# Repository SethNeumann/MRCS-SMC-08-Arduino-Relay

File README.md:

# REPO NAME: MRCS-SMC-08-Arduino-Relay 
## License: Creative Commons Attribution-NonCommercial-ShareAlike

8 channel tortoise driver after Chubb's SMC-12 with Arduino relay input

One of the common use cases for our Arduino Relay Controller is setting up a yard or staging ladder. An Arduino relay is often used
to control power on tracks by steering or simply turning power on or off. Another case is to use the SPDT contacts of a common "Arduino
Relay" to control MTB's MPx series switch machines. This board controls 8 Tortoise-by-Circuitron (TM) stall motors using the circuit 
described by Dr Bruce Chubb MMR in his CMRI Application Handbook V 3.0, pages 7-12 thru 7-17, available from JLC Enterprises 
[this is an excellent reference on Model Railroad control and signaling and should be in the library of EVERY model railroader interested 
in electronics]. 

The design of the SMC is modular where a single LM324 quad Op Amp/Comparator controls a pair of Tortii. I have implemented 8 circuits and provided an input
connector compatible with the most common 8 channel Arduino Relay. In this way your code on the Arduino Relay Controller doesn't need to know
whether the device is a Tortoise or an MPx, you simply use the appropriate board.

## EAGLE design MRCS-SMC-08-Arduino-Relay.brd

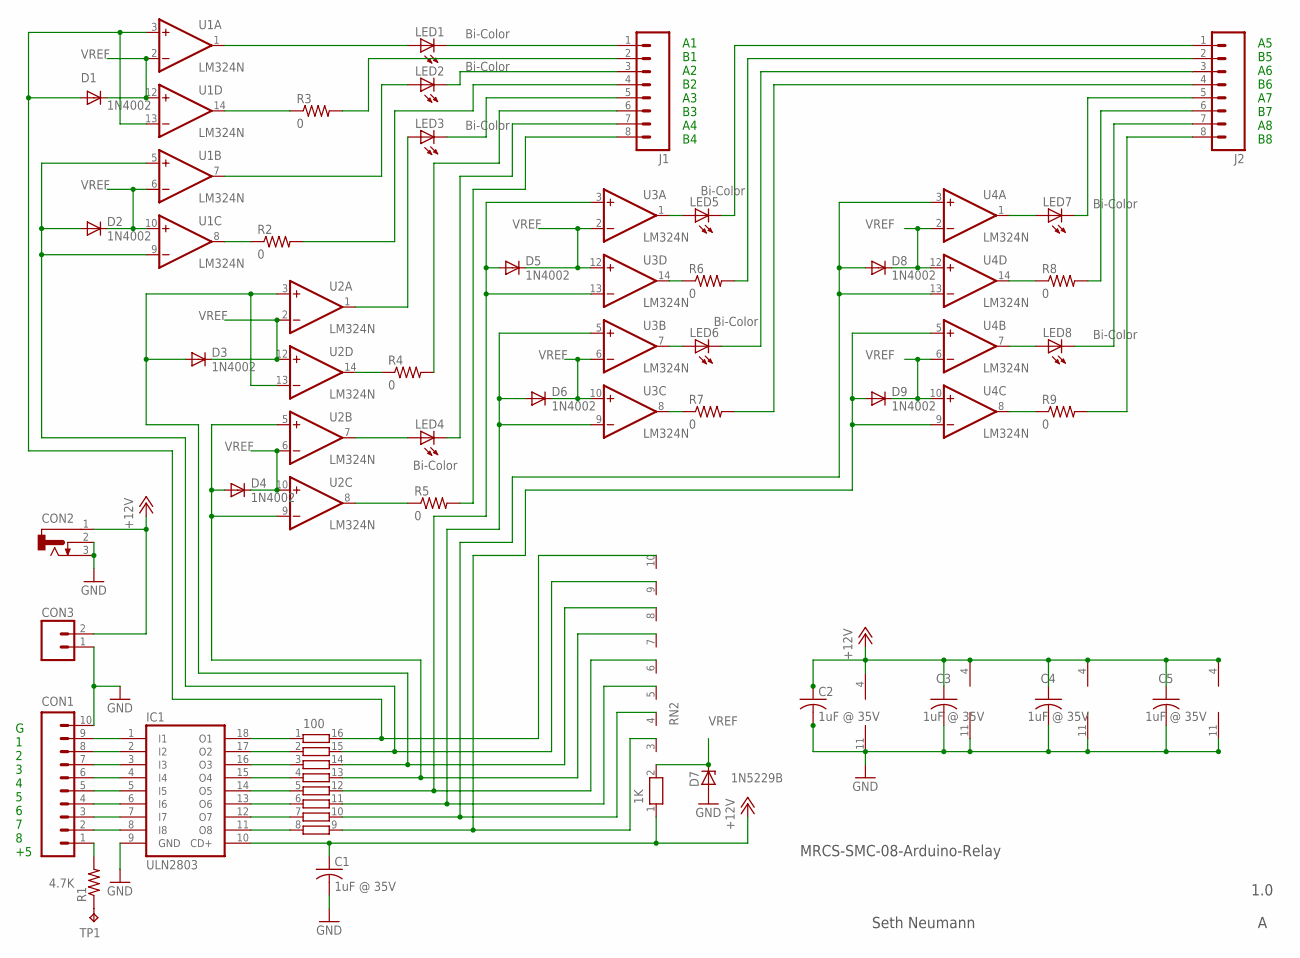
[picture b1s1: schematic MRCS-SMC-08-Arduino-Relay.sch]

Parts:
C1, C2, C3, C4, C5: 1uF @ 35V; C-PTH-0.100
CON1: CONNECTOR-M10LOCK; 1X10_LOCK
CON2: CONNECTOR-DC-POWER-S; DCJ0202-SMALL
CON3: CONNECTOR-M023.5MM-LOCK; SCREWTERMINAL-3.5MM-2_LOCK
D1, D2, D3, D4, D5, D6, D8, D9: 1N4002; DIODE-1N4001
D7: 1N5229B; ZDIO-5
IC1: ULN2803; DIL18
J1, J2: CONNECTOR-M08LOCK; 1X08_LOCK
LED1, LED2, LED3, LED4, LED5, LED6, LED7, LED8: Bi-Color; LED3MM
R1: 4.7K; AXIAL-0.4-RES
R2, R3, R4, R5, R6, R7, R8, R9: 0; CUT-R
RN1: 100; DIL16
RN2: 1K; RN-10
TP1: TPPAD1-13; P1-13
U1, U2, U3, U4: LM324N; DIL14

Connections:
+12V: C1.1, C2.1, C3.1, C4.1, C5.1, CON2.1, CON3.2 (B), IC1.10 (CD+), RN2.1, U1.4 (V+), U2.4 (V+), U3.4 (V+), U4.4 (V+)
GND: C1.2, C2.2, C3.2, C4.2, C5.2, CON1.10, CON2.2, CON2.3, CON3.1 (A), D7.A, IC1.9 (GND), U1.11 (V-), U2.11 (V-), U3.11 (V-), U4.11 (V-)
unnamed: R1.P$1 (1), TP1.TP
unnamed: CON1.9, IC1.1 (I1)
unnamed: CON1.8, IC1.2 (I2)
unnamed: CON1.7, IC1.3 (I3)
unnamed: CON1.6, IC1.4 (I4)
unnamed: CON1.5, IC1.5 (I5)
unnamed: CON1.4, IC1.6 (I6)
unnamed: CON1.3, IC1.7 (I7)
unnamed: CON1.2, IC1.8 (I8)
unnamed: D2.A, RN1.15 (2), RN2.9, U1.5 (+IN), U1.9 (-IN)
unnamed: R3.P2 (1), U1.14 (OUT)
unnamed: CON1.1, R1.P$2 (2)
unnamed: J1.7, LED4.K (C)
unnamed: J1.2, R3.P1 (2)
unnamed: LED1.A, U1.1 (OUT)
unnamed: J1.1, LED1.K (C)
unnamed: IC1.18 (O1), RN1.1
unnamed: IC1.17 (O2), RN1.2 (1)
unnamed: LED2.A, U1.7 (OUT)
unnamed: R2.P2 (1), U1.8 (OUT)
unnamed: J1.4, R2.P1 (2)
unnamed: J1.3, LED2.K (C)
unnamed: IC1.16 (O3), RN1.3 (1)
unnamed: IC1.15 (O4), RN1.4 (1)
unnamed: IC1.14 (O5), RN1.5 (1)
unnamed: IC1.13 (O6), RN1.6 (1)
unnamed: IC1.12 (O7), RN1.7 (1)
unnamed: IC1.11 (O8), RN1.8 (1)
unnamed: LED7.A, U4.1 (OUT)
unnamed: R8.P2 (1), U4.14 (OUT)
unnamed: D6.A, RN1.11 (2), RN2.5, U3.5 (+IN), U3.9 (-IN)
unnamed: LED5.A, U3.1 (OUT)
unnamed: LED4.A, U2.7 (OUT)
unnamed: LED3.A, U2.1 (OUT)
unnamed: D3.A, RN1.14 (2), RN2.8, U2.3 (+IN), U2.13 (-IN)
unnamed: J1.5, LED3.K (C)
unnamed: D1.A, RN1.16 (2), RN2.10, U1.3 (+IN), U1.13 (-IN)
unnamed: R4.P2 (1), U2.14 (OUT)
unnamed: J1.6, R4.P1 (2)
unnamed: D4.A, RN1.13 (2), RN2.7, U2.5 (+IN), U2.9 (-IN)
unnamed: R5.P2 (1), U2.8 (OUT)
unnamed: J1.8, R5.P1 (2)
unnamed: R6.P2 (1), U3.14 (OUT)
unnamed: D5.A, RN1.12 (2), RN2.6, U3.3 (+IN), U3.13 (-IN)
unnamed: J2.1, LED5.K (C)
unnamed: J2.2, R6.P1 (2)
unnamed: LED6.A, U3.7 (OUT)
unnamed: R7.P2 (1), U3.8 (OUT)
unnamed: J2.3, LED6.K (C)
unnamed: J2.4, R7.P1 (2)
unnamed: LED8.A, U4.7 (OUT)
unnamed: J2.6, R8.P1 (2)
unnamed: D8.A, RN1.10 (2), RN2.4, U4.3 (+IN), U4.13 (-IN)
unnamed: D9.A, RN1.9 (2), RN2.3, U4.5 (+IN), U4.9 (-IN)
unnamed: R9.P2 (1), U4.8 (OUT)
unnamed: J2.5, LED7.K (C)
unnamed: J2.7, LED8.K (C)
unnamed: J2.8, R9.P1 (2)
VREF: D1.C, D2.C, D3.C, D4.C, D5.C, D6.C, D7.C, D8.C, D9.C, RN2.2, U1.2 (-IN), U1.6 (-IN), U1.10 (+IN), U1.12 (+IN), U2.2 (-IN), U2.6 (-IN), U2.10 (+IN), U2.12 (+IN), U3.2 (-IN), U3.6 (-IN), U3.10 (+IN), U3.12 (+IN), U4.2 (-IN), U4.6 (-IN), U4.10 (+IN), U4.12 (+IN)

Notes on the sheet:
MRCS-SMC-08-Arduino-Relay
1.0
Seth Neumann
G 1 2 3 4 5 6 7 8 +5
A1 B1 A2 B2 A3 B3 A4 B4
A5 B5 A6 B6 A7 B7 A8 B8

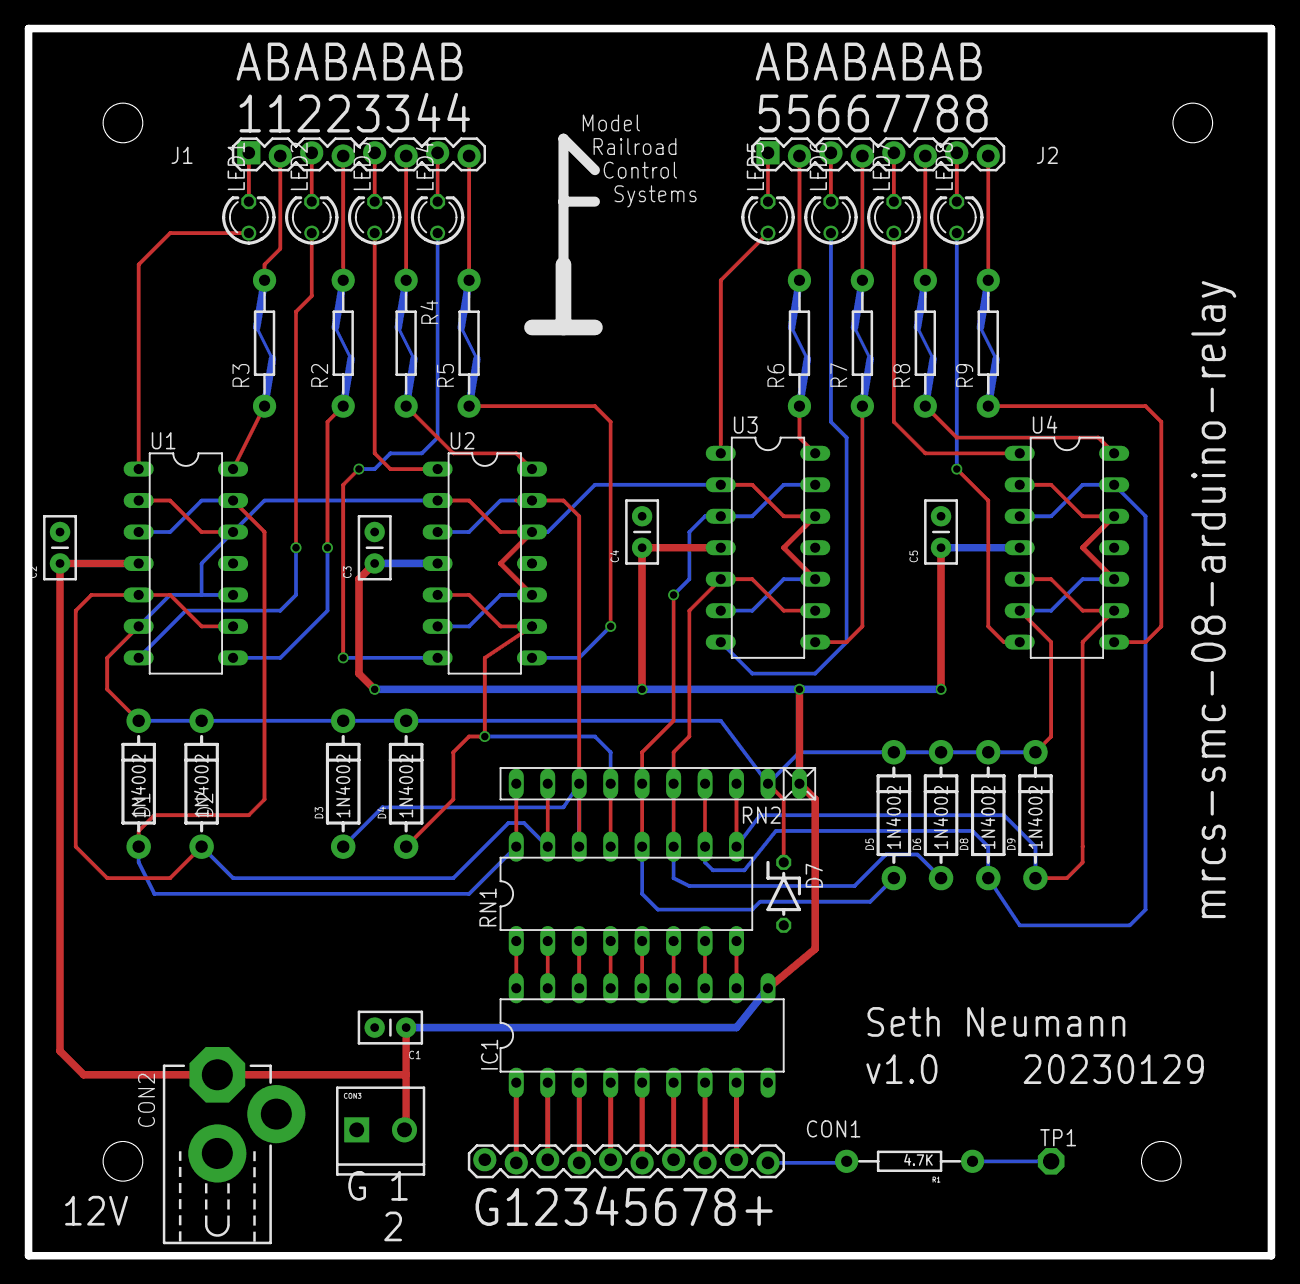
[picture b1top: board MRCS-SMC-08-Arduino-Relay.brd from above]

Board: 2 copper layers, 100.3 x 99.1 mm, 46 parts (0 on the bottom side), 61 nets.

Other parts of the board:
U$1: MRCS-LOGO-LARGE
U$2: MRCSLOGOBTM

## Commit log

2023-01-25 spelling
2023-01-29 First Complete design
    This is the first design, not much optimization here. I kept dimensions at 10x10 to make changes easier.
2023-01-29 added verbiage about input buffering
2023-01-30 initial version sent out for fab
